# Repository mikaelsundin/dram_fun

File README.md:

# dram_fun
Arduino with 512kbyte DRAM memory connected.

Proof of concept. Will use all GPIO on Arduino Nano V3. 

Eagle PCB adapter for Arduino Nano V3. 
Single sided with one jumper.

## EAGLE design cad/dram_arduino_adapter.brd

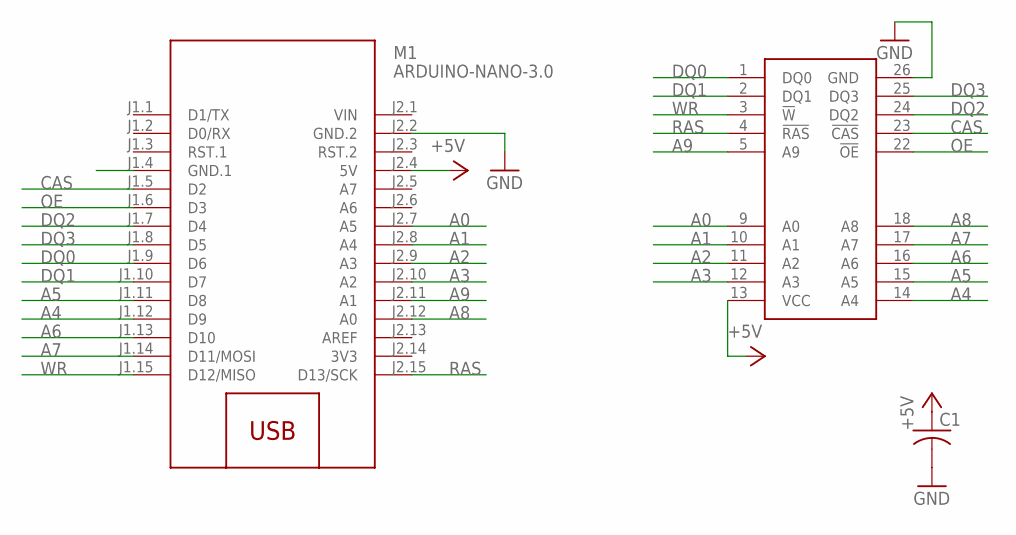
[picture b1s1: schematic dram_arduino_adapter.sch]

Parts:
C1: C-USC1206; C1206
M1: ARDUINO-NANO-3.0
U$1: HY514400A

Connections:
3V3: M1.J2.14 (3V3)
+5V: C1.1, M1.J2.4 (5V), U$1.13 (VCC)
A0: M1.J2.7 (A5), U$1.9 (A0)
A1: M1.J2.8 (A4), U$1.10 (A1)
A2: M1.J2.9 (A3), U$1.11 (A2)
A3: M1.J2.10 (A2), U$1.12 (A3)
A4: M1.J1.12 (D9), U$1.14 (A4)
A5: M1.J1.11 (D8), U$1.15 (A5)
A6: M1.J1.13 (D10), U$1.16 (A6)
A7: M1.J1.14 (D11/MOSI), U$1.17 (A7)
A8: M1.J2.12 (A0), U$1.18 (A8)
A9: M1.J2.11 (A1), U$1.5 (A9)
CAS: M1.J1.5 (D2), U$1.23 (!CAS!)
DQ0: M1.J1.9 (D6), U$1.1 (DQ0)
DQ1: M1.J1.10 (D7), U$1.2 (DQ1)
DQ2: M1.J1.7 (D4), U$1.24 (DQ2)
DQ3: M1.J1.8 (D5), U$1.25 (DQ3)
GND: C1.2, M1.J2.2 (GND.2), U$1.26 (GND)
OE: M1.J1.6 (D3), U$1.22 (!OE!)
RAS: M1.J2.15 (D13/SCK), U$1.4 (!RAS!)
VIN: M1.J2.1 (VIN)
WR: M1.J1.15 (D12/MISO), U$1.3 (!W!)

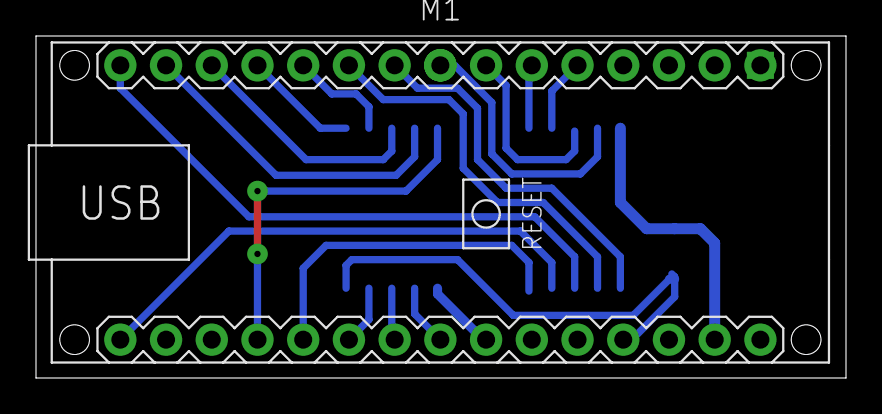
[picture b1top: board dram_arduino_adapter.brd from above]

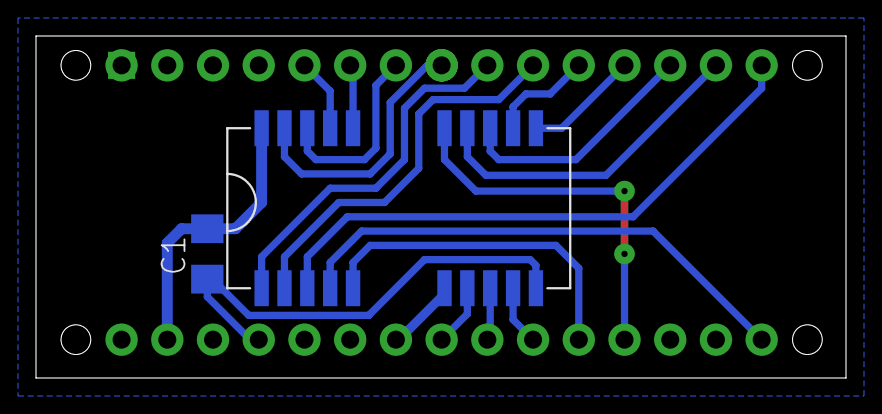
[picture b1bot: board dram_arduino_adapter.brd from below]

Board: 2 copper layers, 45.0 x 19.0 mm, 3 parts (2 on the bottom side), 20 nets.

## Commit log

2020-05-10 Added code, dram_arduino_adapter pcb and some datasheet on HY514400A 5V 1Mx4 DRAM chip.
2020-05-10 Addded PCB photo.

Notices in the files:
parts and their libraries:
diy-modules: Released under the Creative Commons Attribution 4.0 International License: http://creativecommons.org/licenses/by/4.0
